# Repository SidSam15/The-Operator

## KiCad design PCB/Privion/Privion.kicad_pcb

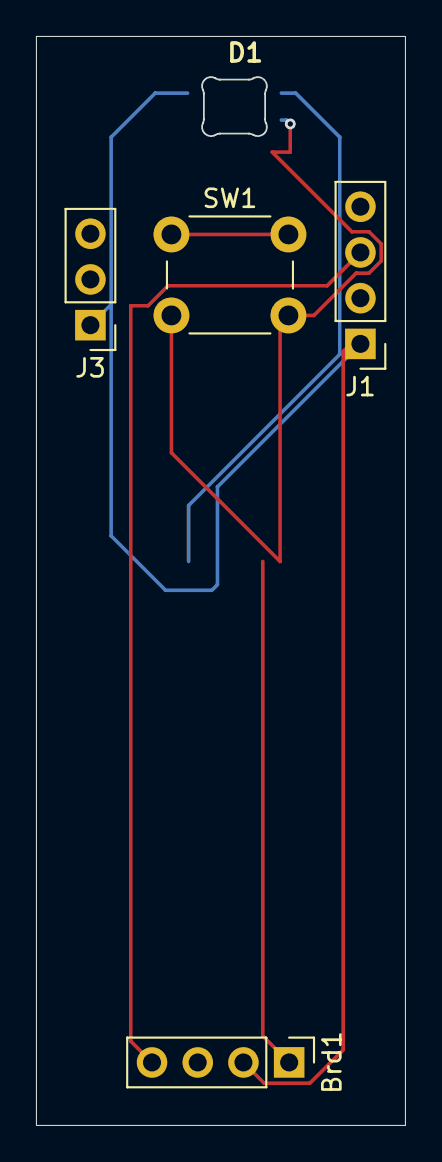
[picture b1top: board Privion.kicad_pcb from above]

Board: 2 copper layers, 20.5 x 60.5 mm, 5 parts (0 on the bottom side), 3 nets.

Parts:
Brd1: SSD1306; PinHeader_1x04_P2.54mm_Vertical
D1: SK6812MINI-E; SK6812MINI-E_fixed
J1: Conn_02x20_Odd_Even; PinHeader_1x04_P2.54mm_Vertical
J3: Conn_01x03; PinHeader_1x03_P2.54mm_Vertical
SW1: SW_Push; SW_PUSH_6mm

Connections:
GND: Brd1.1 (GND), D1.3 (VSS), SW1.2
GPIO2: Brd1.4 (SDA), J1.3
LEDPOWER: Brd1.2 (VCC), D1.1 (VDD), J1.1, J3.1
